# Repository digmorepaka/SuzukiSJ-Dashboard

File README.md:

# SuzukiSJ-Dashboard
Insert module for a Suzuki SJ Jimny/Samurai '86-88.0 Instrument cluster with communications to speeduino ECU
ST7789 LCD

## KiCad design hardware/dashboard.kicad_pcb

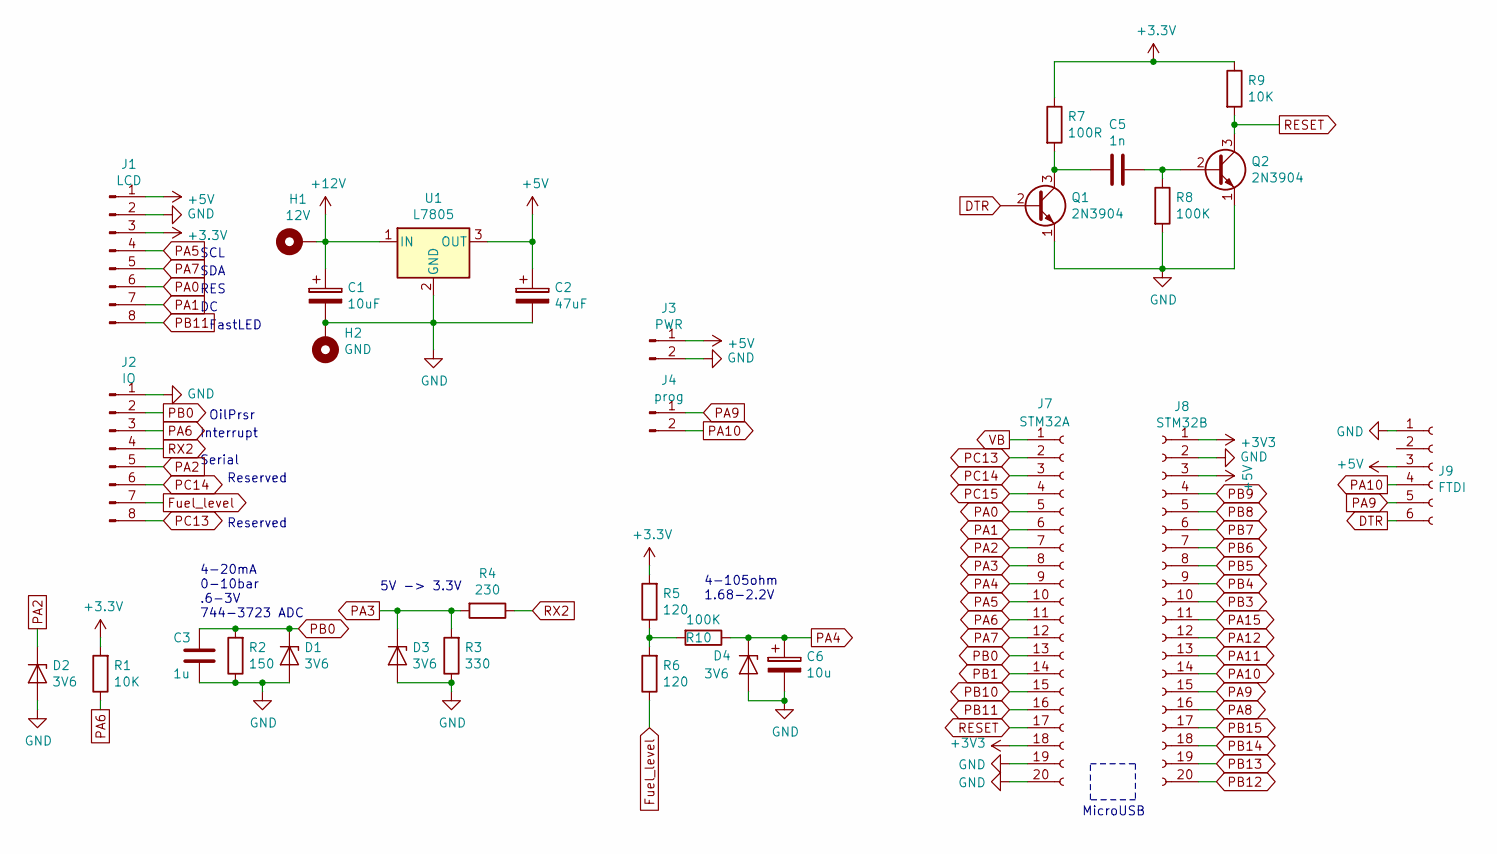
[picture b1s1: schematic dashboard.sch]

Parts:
C1: 10uF; CP_Radial_Tantal_D6.0mm_P2.50mm
C2: 47uF; CP_Radial_Tantal_D6.0mm_P2.50mm
C3: 1u; C_Axial_L5.1mm_D3.1mm_P7.50mm_Horizontal
C5: 1n; C_Axial_L5.1mm_D3.1mm_P7.50mm_Horizontal
C6: 10u; CP_Radial_Tantal_D6.0mm_P2.50mm
D1, D2, D3, D4: 3V6; D_DO-15_P10.16mm_Horizontal
H1: 12V; MountingHole_4.3x6.2mm_M4_Pad_Via
H2: GND; MountingHole_4.3x6.2mm_M4_Pad_Via
J1: LCD; PinHeader_1x08_P2.54mm_Vertical
J2: IO; PinHeader_1x08_P2.54mm_Vertical
J3: PWR; PinSocket_1x02_P2.54mm_Vertical
J4: prog; PinSocket_1x02_P2.54mm_Vertical
J7: STM32A; PinSocket_1x20_P2.54mm_Vertical
J8: STM32B; PinSocket_1x20_P2.54mm_Vertical
J9: FTDI; PinSocket_1x06_P2.54mm_Vertical
Q1, Q2: 2N3904; TO-92_Inline
R1, R9: 10K; R_Axial_DIN0207_L6.3mm_D2.5mm_P7.62mm_Horizontal
R2: 150; R_Axial_DIN0207_L6.3mm_D2.5mm_P7.62mm_Horizontal
R3: 330; R_Axial_DIN0207_L6.3mm_D2.5mm_P7.62mm_Horizontal
R4: 230; R_Axial_DIN0207_L6.3mm_D2.5mm_P7.62mm_Horizontal
R5, R6: 120; R_Axial_DIN0207_L6.3mm_D2.5mm_P7.62mm_Horizontal
R7: 100R; R_Axial_DIN0207_L6.3mm_D2.5mm_P7.62mm_Horizontal
R8, R10: 100K; R_Axial_DIN0207_L6.3mm_D2.5mm_P7.62mm_Horizontal
U1: L7805; TO-220-3_Horizontal_TabDown

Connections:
+5V: C2.1, J1.1, J3.1, J8.3, J9.3, U1.3 (OUT)
+12V: C1.1, H1.1, U1.1 (IN)
DTR: J9.6, Q1.2 (B)
Fuel_level: J2.7, R6.1
GND: C1.2, C2.2, C3.2, C6.2, D1.2 (A), D2.2 (A), D3.2 (A), D4.2 (A), H2.1, J1.2, J2.1, J3.2, J7.19, J7.20, J8.2, J9.1, Q1.1 (E), Q2.1 (E), R2.1, R3.1, R8.2, U1.2 (GND)
unnamed: C5.1, Q2.2 (B), R8.1
unnamed: C5.2, Q1.3 (C), R7.2
unnamed: R5.1, R6.2, R10.2
PA0: J1.6, J7.5
PA1: J1.7, J7.6
PA2: D2.1 (K), J2.5, J7.7
PA3: D3.1 (K), J7.8, R3.2, R4.2
PA4: C6.1, D4.1 (K), J7.9, R10.1
PA5: J1.4, J7.10
PA6: J2.3, J7.11, R1.1
PA7: J1.5, J7.12
PA8: J8.16
PA9: J4.1, J8.15, J9.5
PA10: J4.2, J8.14, J9.4
PA11: J8.13
PA12: J8.12
PA15: J8.11
PB0: C3.1, D1.1 (K), J2.2, J7.13, R2.2
PB1: J7.14
PB3: J8.10
PB4: J8.9
PB5: J8.8
PB6: J8.7
PB7: J8.6
PB8: J8.5
PB9: J8.4
PB10: J7.15
PB11: J1.8, J7.16
PB12: J8.20
PB13: J8.19
PB14: J8.18
PB15: J8.17
PC13: J2.8, J7.2
PC14: J2.6, J7.3
PC15: J7.4
RESET: J7.17, Q2.3 (C), R9.2
RX2: J2.4, R4.1
VB: J7.1

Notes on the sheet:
OilPrsr
Interrupt
Serial
Reserved
SCL
SDA
RES
FastLED
4-20mA 0-10bar .6-3V 744-3723 ADC
5V -> 3.3V
4-105ohm 1.68-2.2V
MicroUSB

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
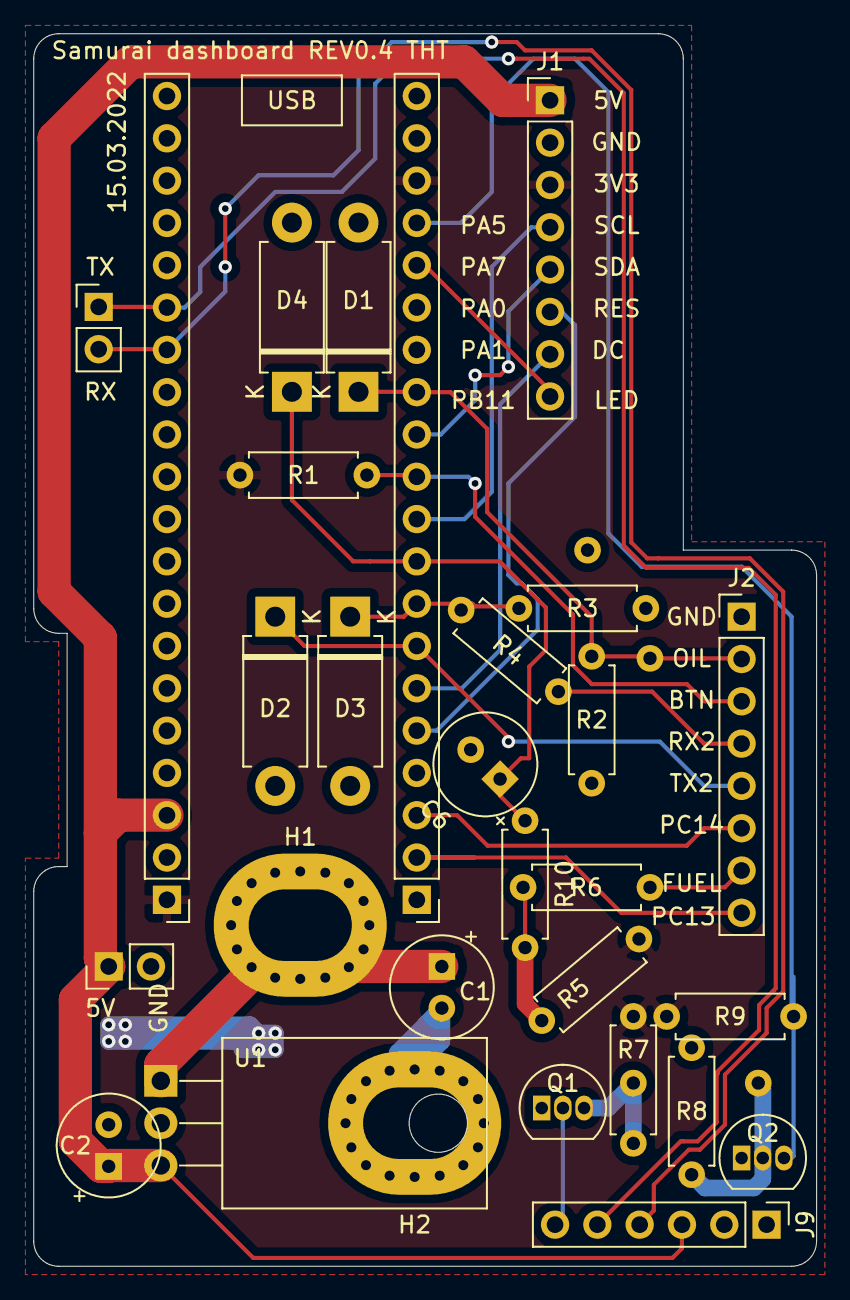
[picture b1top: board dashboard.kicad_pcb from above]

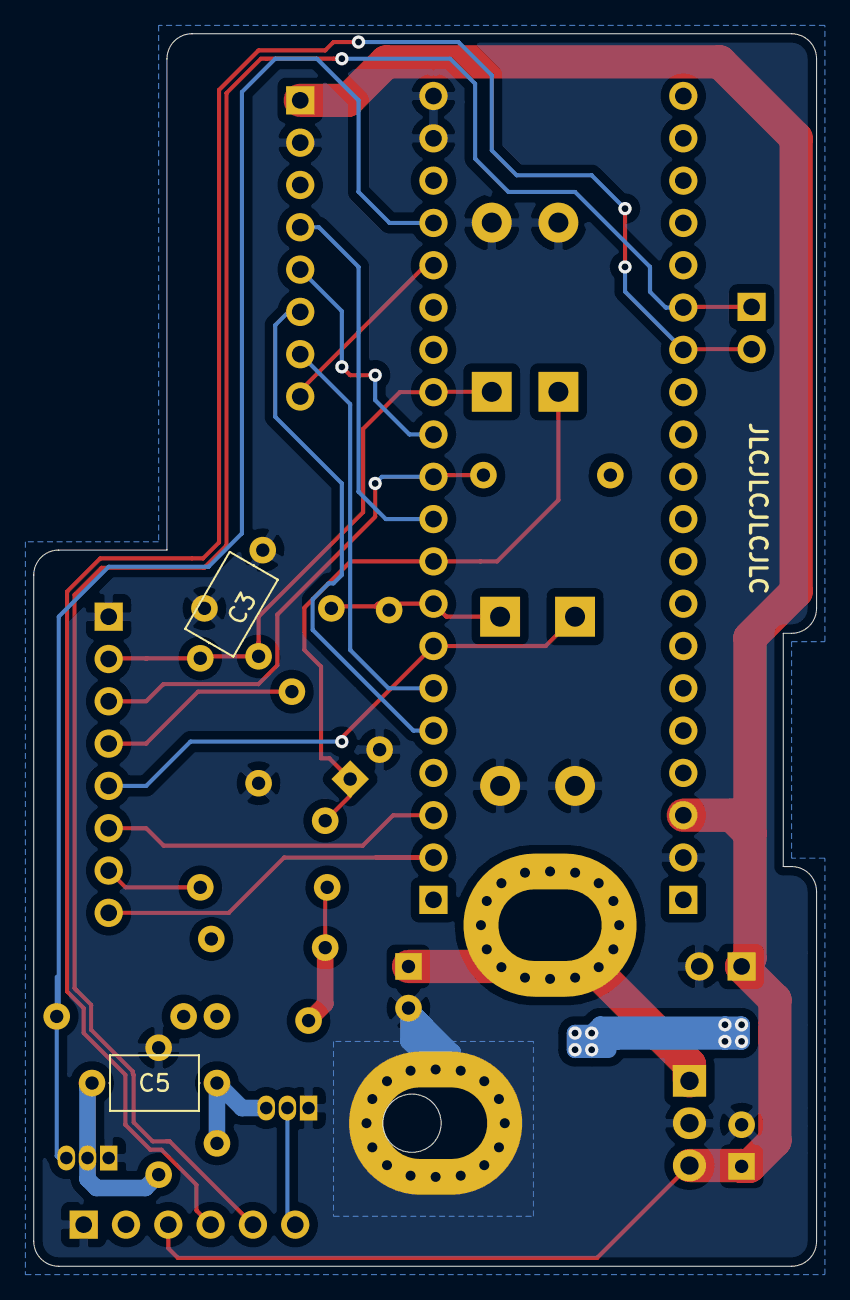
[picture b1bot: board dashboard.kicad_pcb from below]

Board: 2 copper layers, 47.0 x 74.0 mm, 31 parts (2 on the bottom side), 25 nets.

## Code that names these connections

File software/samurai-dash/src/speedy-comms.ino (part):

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#include "MainScreen.h"
#include "TuneScreen.h"

Adafruit_NeoPixel pixels = Adafruit_NeoPixel(3, PB11, NEO_GRB + NEO_KHZ800);

TFT_eSPI tft = TFT_eSPI();
HardwareSerial Serial2(USART2); // for some reason this isn't defined in arduino_core_stm32
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    // Speeduino init
    Serial2.begin(115200); // baudrate for Speeduino is 115200

    pinMode(PB0, INPUT_ANALOG);
    pinMode(PA4, INPUT_ANALOG);
    pinMode(PA6, INPUT_PULLUP);
    attachInterrupt(digitalPinToInterrupt(PA6), addUI, FALLING);
    analogReadResolution(12);
    // Display init
    tft.init(); // initialize a ST7789 chip, 240×240 pixels
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
void updateSensorsData()
{
    fuelraw = analogRead(PA4);
    oilraw = analogRead(PB0);
    // importantData.OILPRSR = map(oilraw,  696, 3675, 0, 100);
    importantData.OILPRSR = (((float)oilraw - 670.0f) / (3675.0f - 670.0f)) * 10.0f; // min max  min
    // Serial2.printf("Data %.2f\n", importantData.OILPRSR);
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
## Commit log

2024-08-30 Add firmware
